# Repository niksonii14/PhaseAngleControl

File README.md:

View this project on [CADLAB.io](https://cadlab.io/project/22560). 

# PhaseAngleControl

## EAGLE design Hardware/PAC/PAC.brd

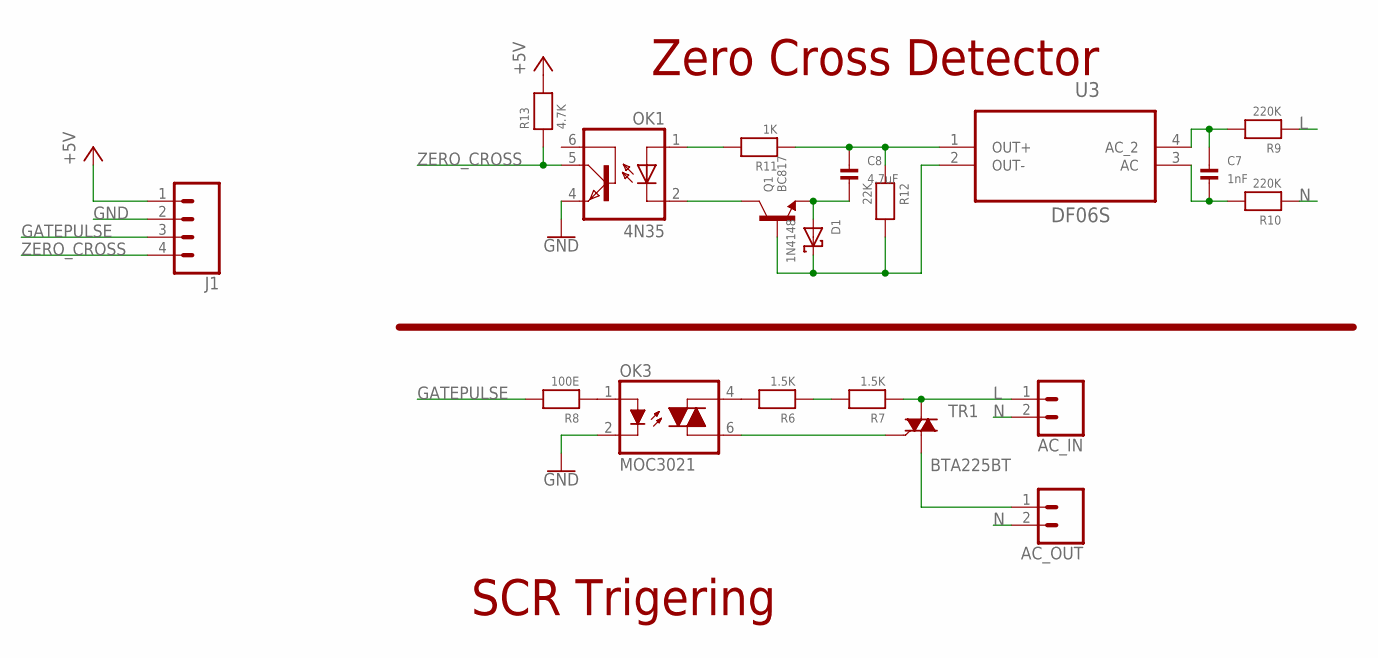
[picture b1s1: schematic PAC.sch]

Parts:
AC_IN: CONN_025MM; SCREWTERMINAL-5MM-2
AC_OUT: CONN_025MM; SCREWTERMINAL-5MM-2
C7: 1nF; 1206; MPN CC1206KKX7RBBB102
C8: 4.7uF; 1206; MPN CC1206KKX7RBBB102
D1: 1N4148; SOD-123; MPN 1N4148W-7-F
J1: CONN_04POLAR; MOLEX-1X4
OK1: 4N35; DIL06; MPN 4N35SR2M
OK3: MOC3021; DIL06; MPN MOC3021SR2VM
Q1: BC817; SOT23-W; MPN BC817-40-TP
R6, R7: 1.5K; 1206; MPN CRGH1206F330R
R8: 100E; 0805; MPN CRCW0805100RFKEB
R9, R10: 220K; 1206; MPN MCWF12P2203FTL
R11: 1K; 0805; MPN CRCW08051K00JNEA
R12: 22K; 0805; MPN RC0805JR-0722KL
R13: 4.7K; 0805; MPN ERJ-P06J472V
TR1: BTA225BT; TO220DS; MPN BTA16-800CWRG
U3: DF06S; SOT508P985X260-4N; MPN DF06S

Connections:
+5V: J1.1, R13.2
GATEPULSE: J1.3, R8.2
GND: J1.2, OK1.4 (EMI), OK3.2 (C)
L: AC_IN.1, R7.1, R9.1, TR1.A2
N: AC_IN.2, AC_OUT.2, R10.1
unnamed: OK3.4 (A2), R6.2
unnamed: R6.1, R7.2
unnamed: OK3.6 (A1), TR1.G
unnamed: OK3.1 (A), R8.1
unnamed: AC_OUT.1, TR1.A1
unnamed: C7.1, R9.2, U3.4 (AC_2)
unnamed: C7.2, R10.2, U3.3 (AC)
unnamed: C8.1, R11.1, R12.1, U3.1 (OUT+)
unnamed: OK1.1 (A), R11.2
unnamed: OK1.2 (C), Q1.3 (C)
unnamed: C8.2, D1.A, Q1.2 (E)
unnamed: D1.C, Q1.1 (B), R12.2, U3.2 (OUT-)
ZERO_CROSS: J1.4, OK1.5 (COL), R13.1

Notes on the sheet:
SCR Trigering
Zero Cross Detector

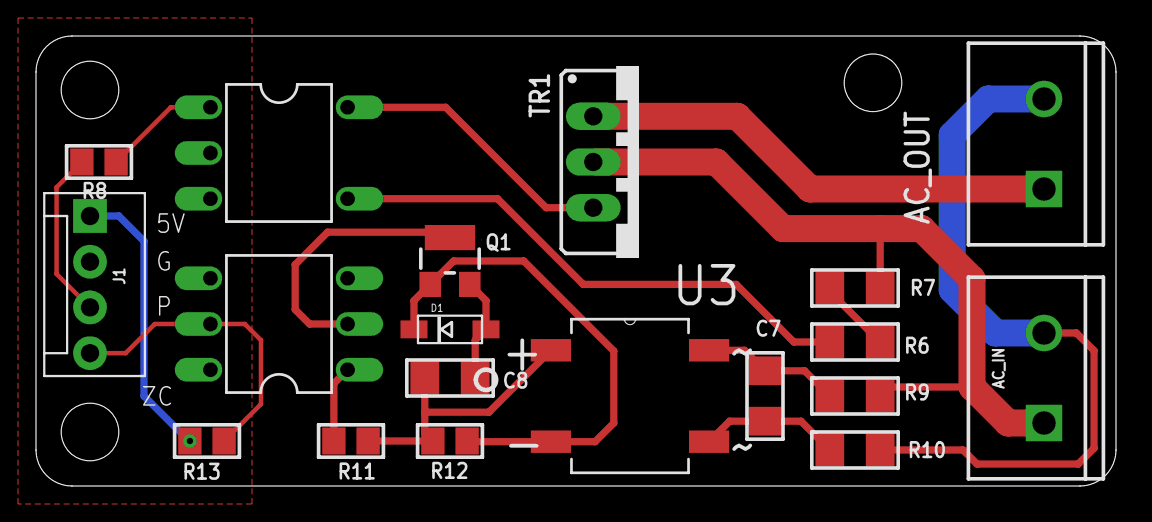
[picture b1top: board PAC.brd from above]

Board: 2 copper layers, 60.0 x 25.0 mm, 19 parts (0 on the bottom side), 18 nets.

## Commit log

2018-11-01 Update PhaseAngleControl.ino
    update
2019-11-19 Eagle PCB Project
2019-11-19 PhaseAngleControl
2020-01-01 New codes for AC light control
2020-01-30 code update
2020-03-03 Backlink to CADLAB.io has been added.
2020-06-15 Set theme jekyll-theme-cayman

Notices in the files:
parts and their libraries:
microbuilder: This work is placed in the public domain, and may be freely used for commercial and non-commercial work with the following conditions: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
SparkFun-Connectors: Licensing: Creative Commons ShareAlike 4.0 International - https://creativecommons.org/licenses/by-sa/4.0
